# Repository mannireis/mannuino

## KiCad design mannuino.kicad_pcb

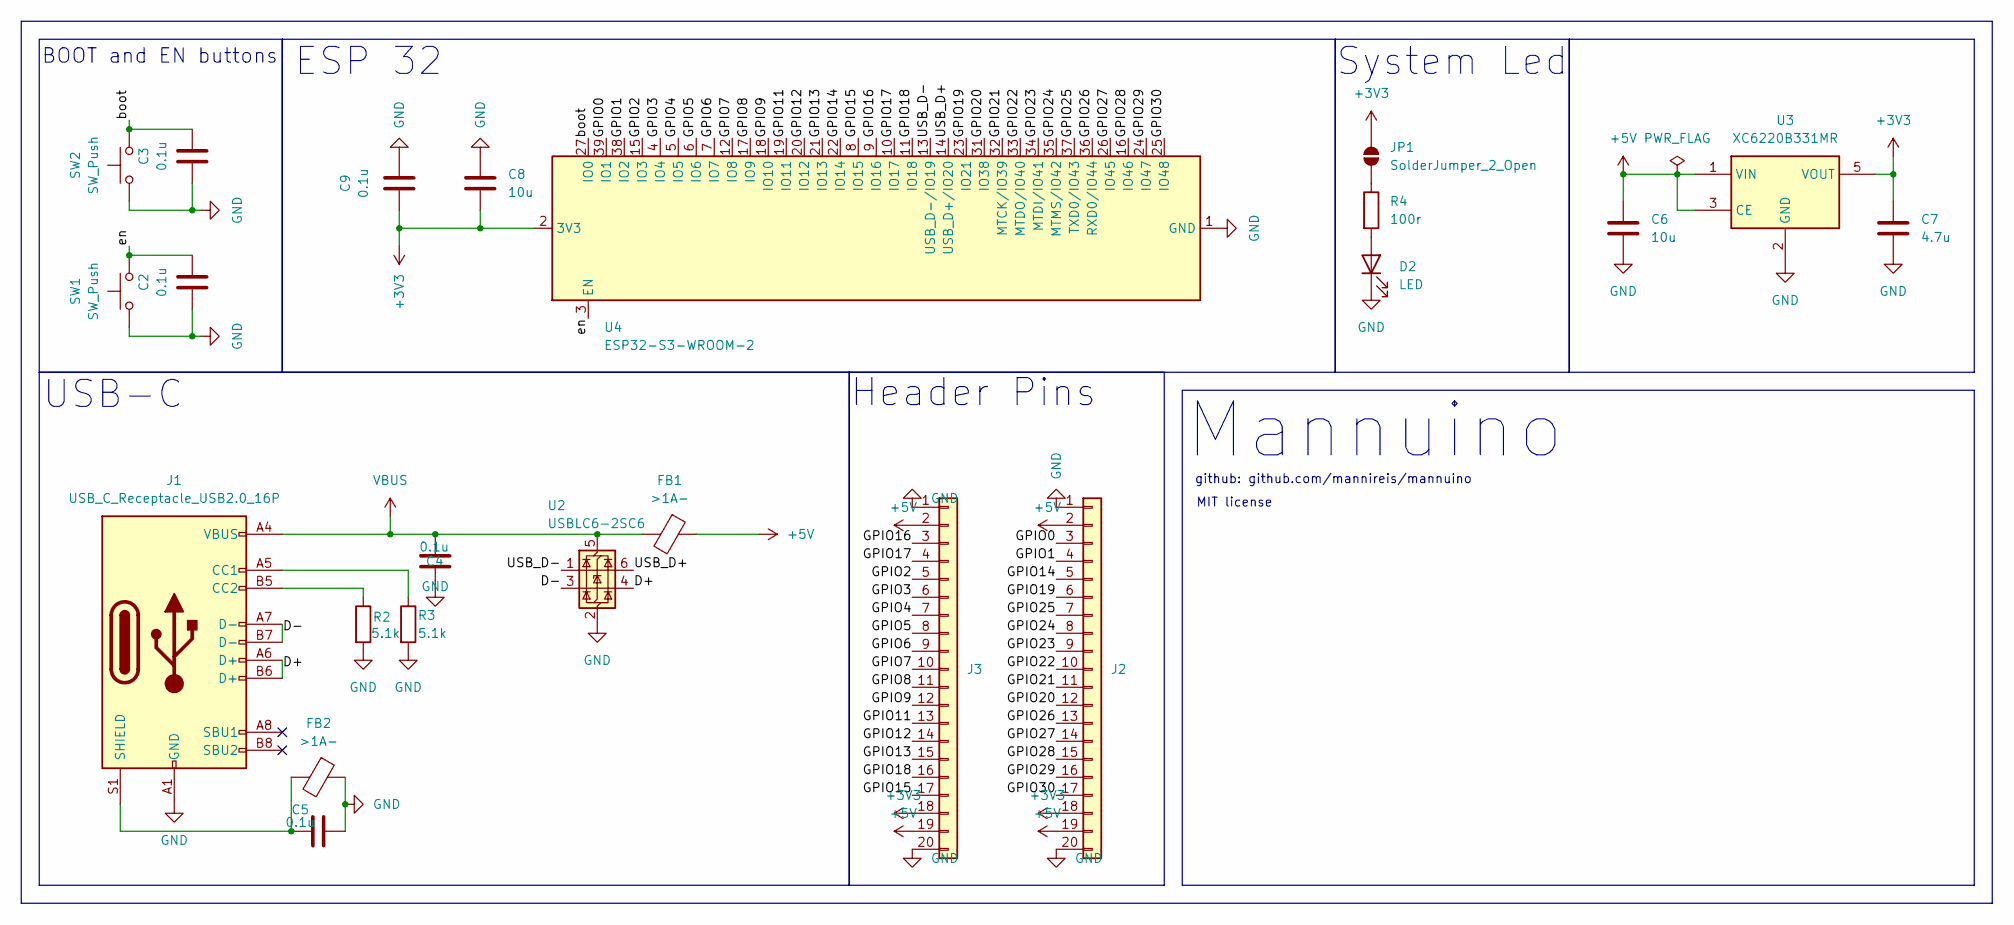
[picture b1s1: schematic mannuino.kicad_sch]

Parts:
C2, C3, C4, C5, C9: 0.1u; C_0805_2012Metric
C6: 10u; C_0805_2012Metric
C7: 4.7u; C_1206_3216Metric
C8: 10u; C_0402_1005Metric
D2: LED; LED_0201_0603Metric
FB1, FB2: >1A-; L_1206_3216Metric
J1: USB_C_Receptacle_USB2.0_16P; USB_C_Receptacle_Molex_105450-0101
J2, J3: Conn_01x20; PinHeader_1x20_P2.00mm_Vertical
JP1: SolderJumper_2_Open; SolderJumper-2_P1.3mm_Open_Pad1.0x1.5mm
R2, R3: 5.1k; R_0603_1608Metric
R4: 100r; R_0603_1608Metric
SW1, SW2: SW_Push; SW_Push_1P1T_NO_CK_KMR2
U2: USBLC6-2SC6; SOT-23-6
U3: XC6220B331MR; SOT-23-5
U4: ESP32-S3-WROOM-2; ESP32-S3-WROOM-1U

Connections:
+3V3: C7.1, C8.1, C9.1, J2.18, J3.18, JP1.2 (B), U3.5 (VOUT), U4.2 (3V3)
+5V: C6.1, FB1.1, J2.2, J2.19, J3.2, J3.19, U3.1 (VIN), U3.3 (CE)
/D+: J1.A6 (D+), J1.B6 (D+), U2.4 (I/O2)
/D-: J1.A7 (D-), J1.B7 (D-), U2.3 (I/O2)
/GPIO0: J2.3, U4.39 (IO1)
/GPIO1: J2.4, U4.38 (IO2)
/GPIO2: J3.5, U4.15 (IO3)
/GPIO3: J3.6, U4.4 (IO4)
/GPIO4: J3.7, U4.5 (IO5)
/GPIO5: J3.8, U4.6 (IO6)
/GPIO6: J3.9, U4.7 (IO7)
/GPIO7: J3.10, U4.12 (IO8)
/GPIO8: J3.11, U4.17 (IO9)
/GPIO9: J3.12, U4.18 (IO10)
/GPIO11: J3.13, U4.19 (IO11)
/GPIO12: J3.14, U4.20 (IO12)
/GPIO13: J3.15, U4.21 (IO13)
/GPIO14: J2.5, U4.22 (IO14)
/GPIO15: J3.17, U4.8 (IO15)
/GPIO16: J3.3, U4.9 (IO16)
/GPIO17: J3.4, U4.10 (IO17)
/GPIO18: J3.16, U4.11 (IO18)
/GPIO19: J2.6, U4.23 (IO21)
/GPIO20: J2.12, U4.31 (IO38)
/GPIO21: J2.11, U4.32 (MTCK/IO39)
/GPIO22: J2.10, U4.33 (MTDO/IO40)
/GPIO23: J2.9, U4.34 (MTDI/IO41)
/GPIO24: J2.8, U4.35 (MTMS/IO42)
/GPIO25: J2.7, U4.37 (TXD0/IO43)
/GPIO26: J2.13, U4.36 (RXD0/IO44)
/GPIO27: J2.14, U4.26 (IO45)
/GPIO28: J2.15, U4.16 (IO46)
/GPIO29: J2.16, U4.24 (IO47)
/GPIO30: J2.17, U4.25 (IO48)
/USB_D+: U2.6 (I/O1), U4.14 (USB_D+/IO20)
/USB_D-: U2.1 (I/O1), U4.13 (USB_D-/IO19)
/boot: C3.1, SW2.2, U4.27 (IO0)
/en: C2.1, SW1.2, U4.3 (EN)
GND: C2.2, C3.2, C4.2, C5.2, C6.2, C7.2, C8.2, C9.2, D2.1 (K), FB2.1, J1.A1 (GND), J1.A12 (GND), J1.B1 (GND), J1.B12 (GND), J2.1, J2.20, J3.1, J3.20, R2.2, R3.2, SW1.1, SW2.1, U2.2 (GND), U3.2 (GND), U4.1 (GND), U4.40 (GND), U4.41 (GND)
unnamed: D2.2 (A), R4.2
unnamed: J1.A5 (CC1), R3.1
unnamed: J1.B5 (CC2), R2.1
unnamed: C5.1, FB2.2, J1.S1 (SHIELD)
unnamed: JP1.1 (A), R4.1
VBUS: C4.1, FB1.2, J1.A4 (VBUS), J1.A9 (VBUS), J1.B4 (VBUS), J1.B9 (VBUS), U2.5 (VBUS)

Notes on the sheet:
MIT license
Mannuino
Header Pins
ESP 32
BOOT and EN buttons
github: github.com/mannireis/mannuino
USB-C
System Led

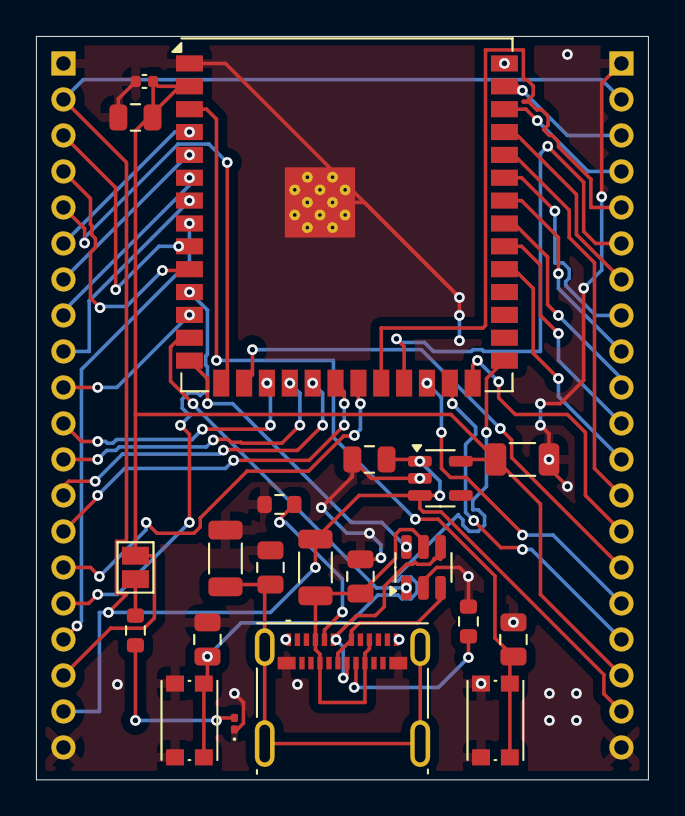
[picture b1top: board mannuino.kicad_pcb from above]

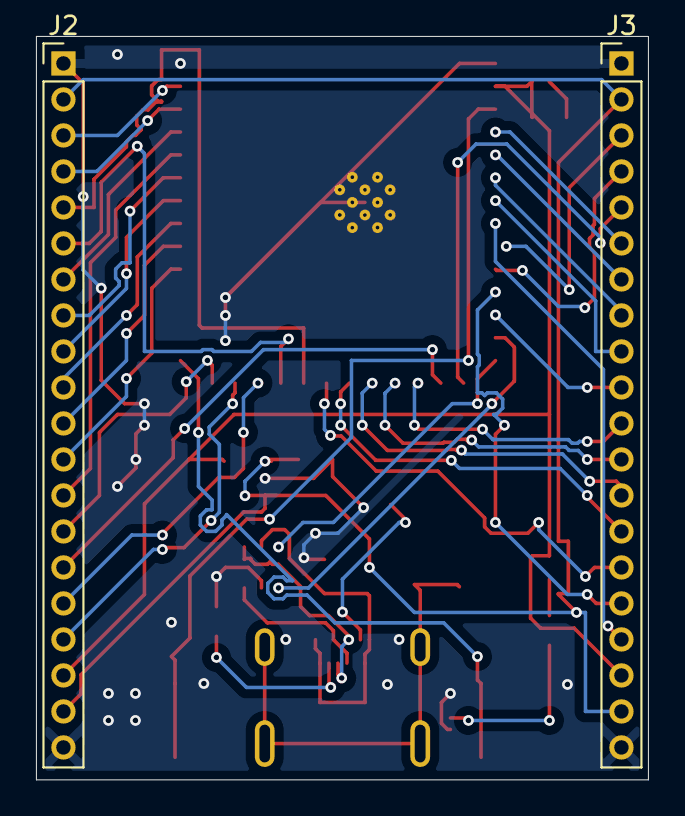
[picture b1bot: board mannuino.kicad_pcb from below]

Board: 2 copper layers, 34.0 x 41.3 mm, 23 parts (2 on the bottom side), 45 nets.

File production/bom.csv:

Designator,Footprint,Quantity,Value,LCSC Part #
"C2, C3, C4, C5, C9",0805,5,0.1u,
C6,0805,1,10u,
C7,1206,1,4.7u,
C8,0402,1,10u,
D2,0201,1,LED,
"FB1, FB2",1206,2,>1A-,
J1,USB_C_Receptacle_Molex_105450-0101,1,USB_C_Receptacle_USB2.0_16P,
"J2, J3",PinHeader_1x20_P2.00mm_Vertical,2,Conn_01x20,
"R2, R3",0603,2,5.1k,
R4,0603,1,100r,
"SW1, SW2",SW_Push_1P1T_NO_CK_KMR2,2,SW_Push,
U2,SOT-23-6,1,USBLC6-2SC6,
U3,SOT-23-5,1,XC6220B331MR,
U4,ESP32-S3-WROOM-1U,1,ESP32-S3-WROOM-2,

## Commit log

2025-05-14 add kicad files
2025-05-20 :heavysob:
2025-05-24 IG last version
2025-05-24 Fix a few things with the pcb
